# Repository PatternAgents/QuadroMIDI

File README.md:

# QuadroMIDI - Four channel MIDI Trigger I/O

Format : ERA / Eurorack / Breadboard Friendly

Height : 1U 

Width: 16HP

Depth : 1.0 cm

Power : +12V 40mA, -12V 40mA

Jacks : Thonkiconn Jacks (PJ301M-12)

The QuadroMIDI is a low cost, embeddable MIDI Trigger module

* Embedded Rack Architecture (Eurorack compatible)
* Optically Isolated MIDI Input Jack
* Driven MIDI Output Jack
* MIDI Clock Output Jack
* MIDI Run/Stop Output Jack
* Four (4) DC coupled  Trigger input channels
* Four (4) DC coupled  Trigger output channels
* Add an optional Front-Panel board for mounting in ERA and/or Eurorack enclosures

[QuadroMIDI](https://github.com/patternagents/QuadroMIDI)

**thingSoC ERA** are OEM friendly implementations that implement various reference 
circuits for demonstrating the use of the PatternAgents IP and Libraries.

---------------------------------------
## QuadroMIDI Applications <a name="QuadroMIDI_Applications"/>

* MIDI to Trigger (Drum Piezo or other Human Interface)
* Add-on board for QuadroTeenia (MIDI I/O and Trigger I/O)

---------------------------------------
## QuadroMIDI Status <a name="QuadroMIDI_Status"/>

**4/10/2018:** 
Revision 1.0.0 - Initial Layout sent from OSHpark

---------------------------------------
## QuadroMIDI Model Images

[QuadroMIDI](https://github.com/patternagents/QuadroMIDI)

[QuadroMIDI](https://github.com/patternagents/QuadroMIDI)

---------------------------------------

## QuadroMIDI Documentation Index <a name="QuadroMIDI_documentation_index"/>

[QuadroMIDI Project](http://thingsoc.github.io/projects/QuadroMIDI.html)

[QuadroMIDI Hardware](https://github.com/patternagents/QuadroMIDI/tree/master/QuadroMIDI/revisions/R1_0_0)

---------------------------------------

## Documentation Index <a name="documentation_index"/>

[Organization Website](http://patternagents.github.io)

[FAQ - Frequently Asked Questions](http://thingsoc.github.io/support/faq.html)

---------------------------------------

[ 
*PatternAgents, LLC*](http://thingsoc.github.io)

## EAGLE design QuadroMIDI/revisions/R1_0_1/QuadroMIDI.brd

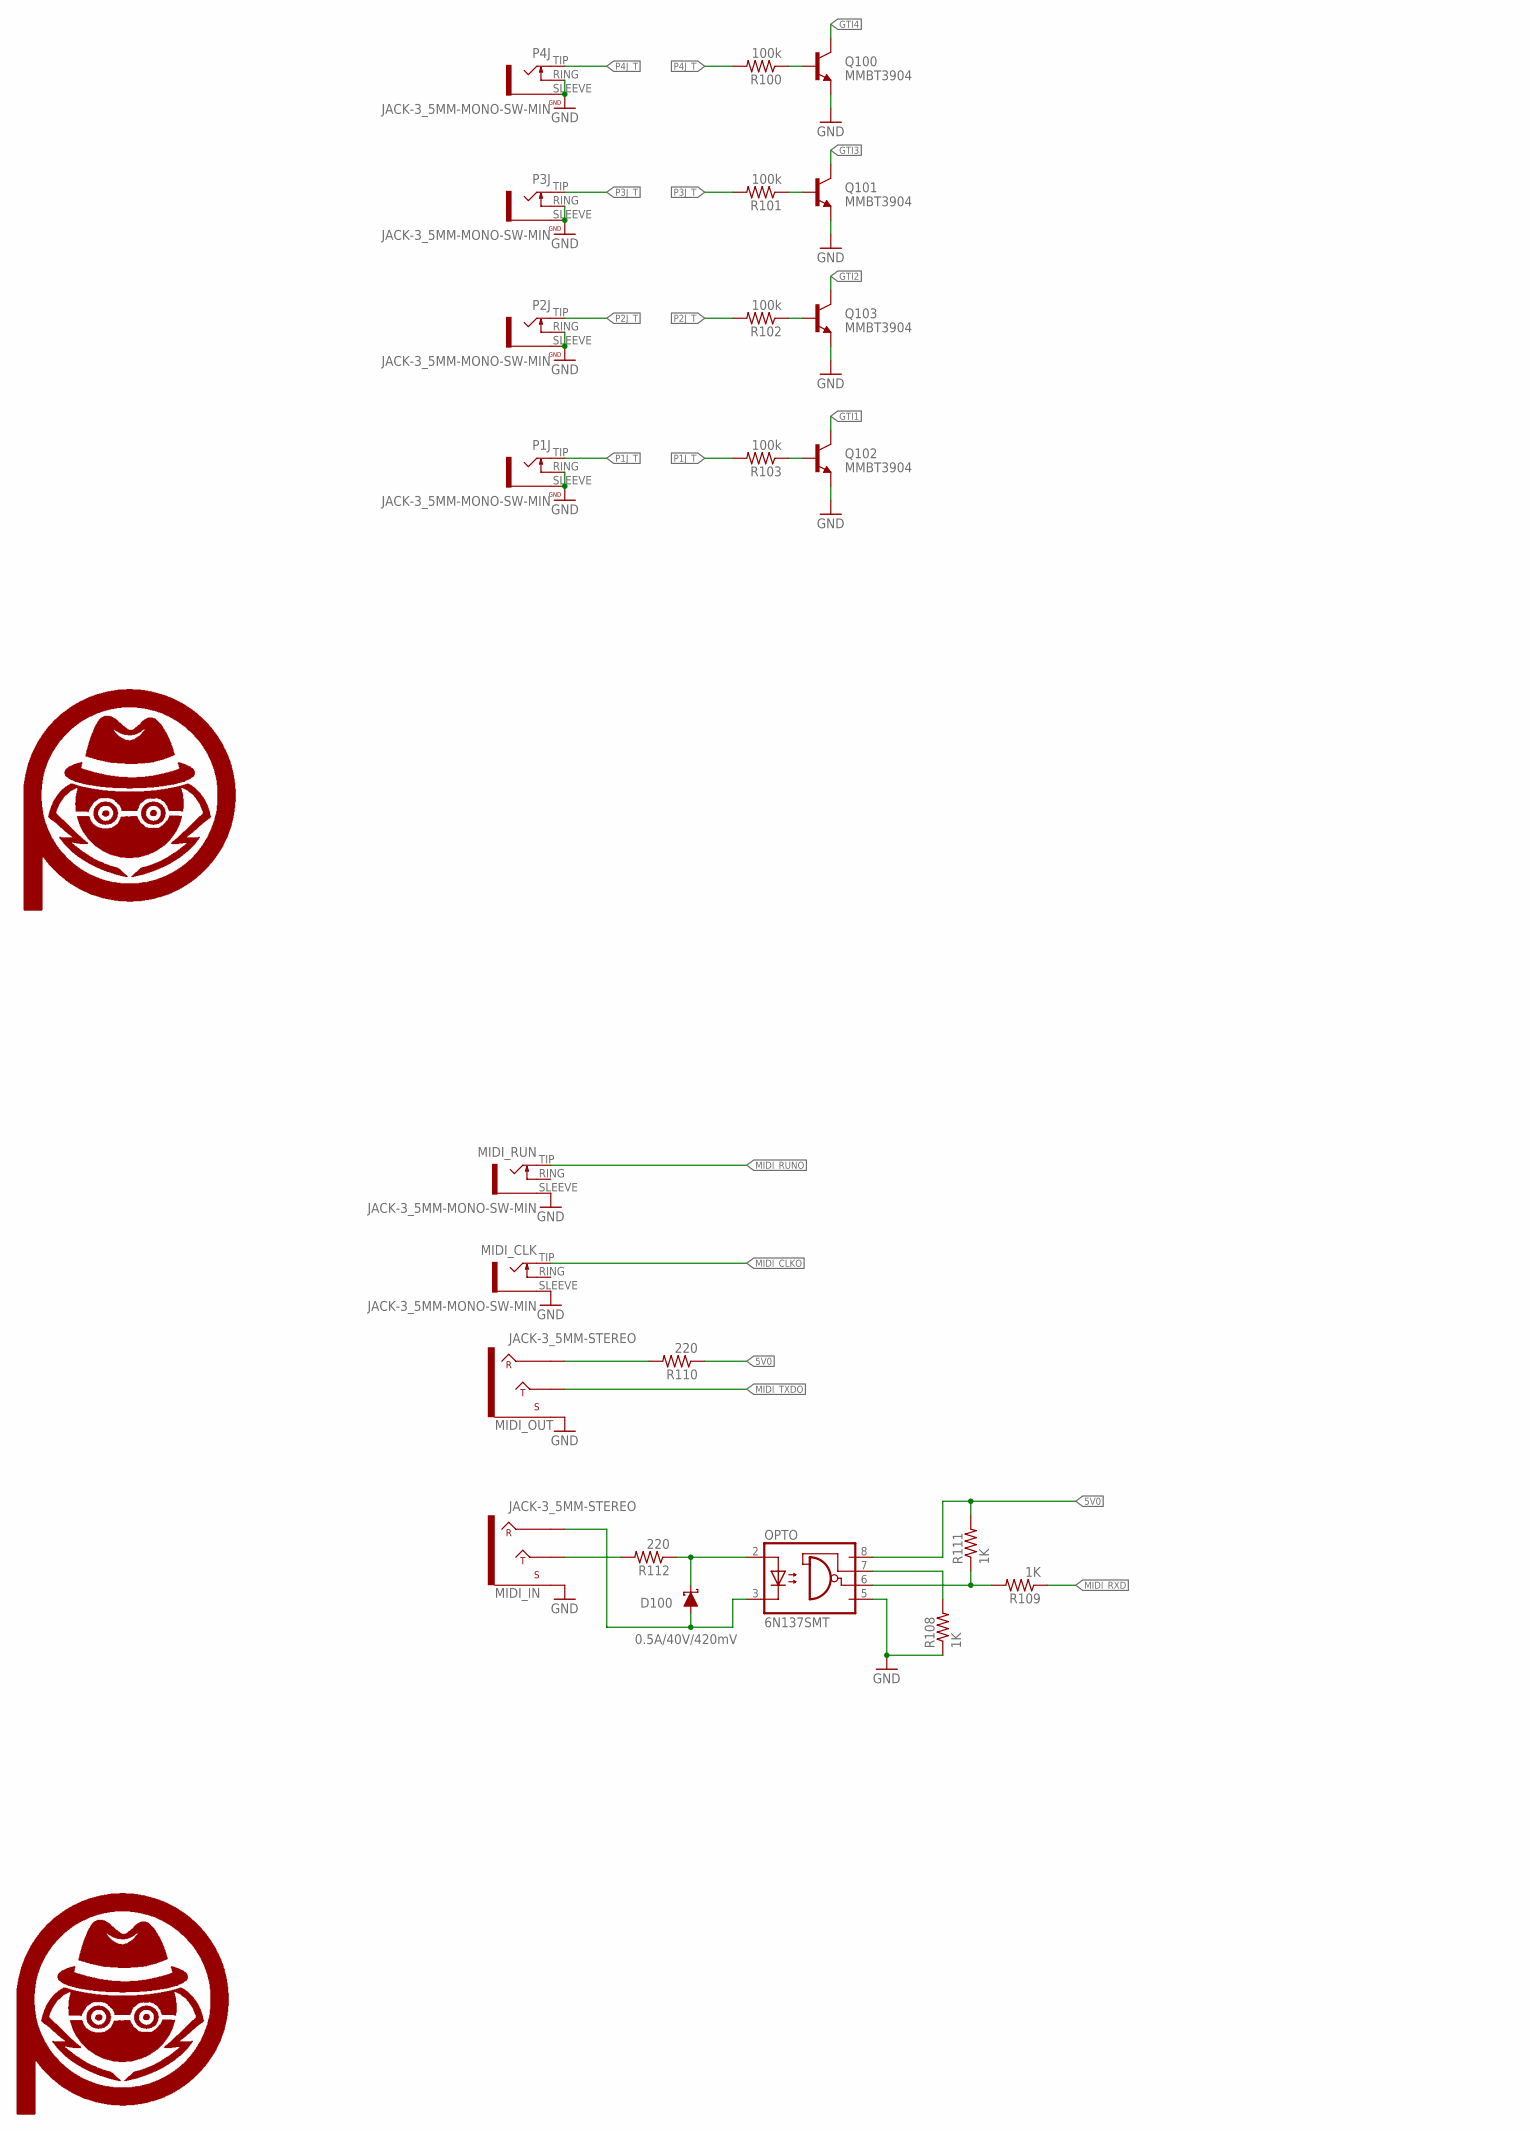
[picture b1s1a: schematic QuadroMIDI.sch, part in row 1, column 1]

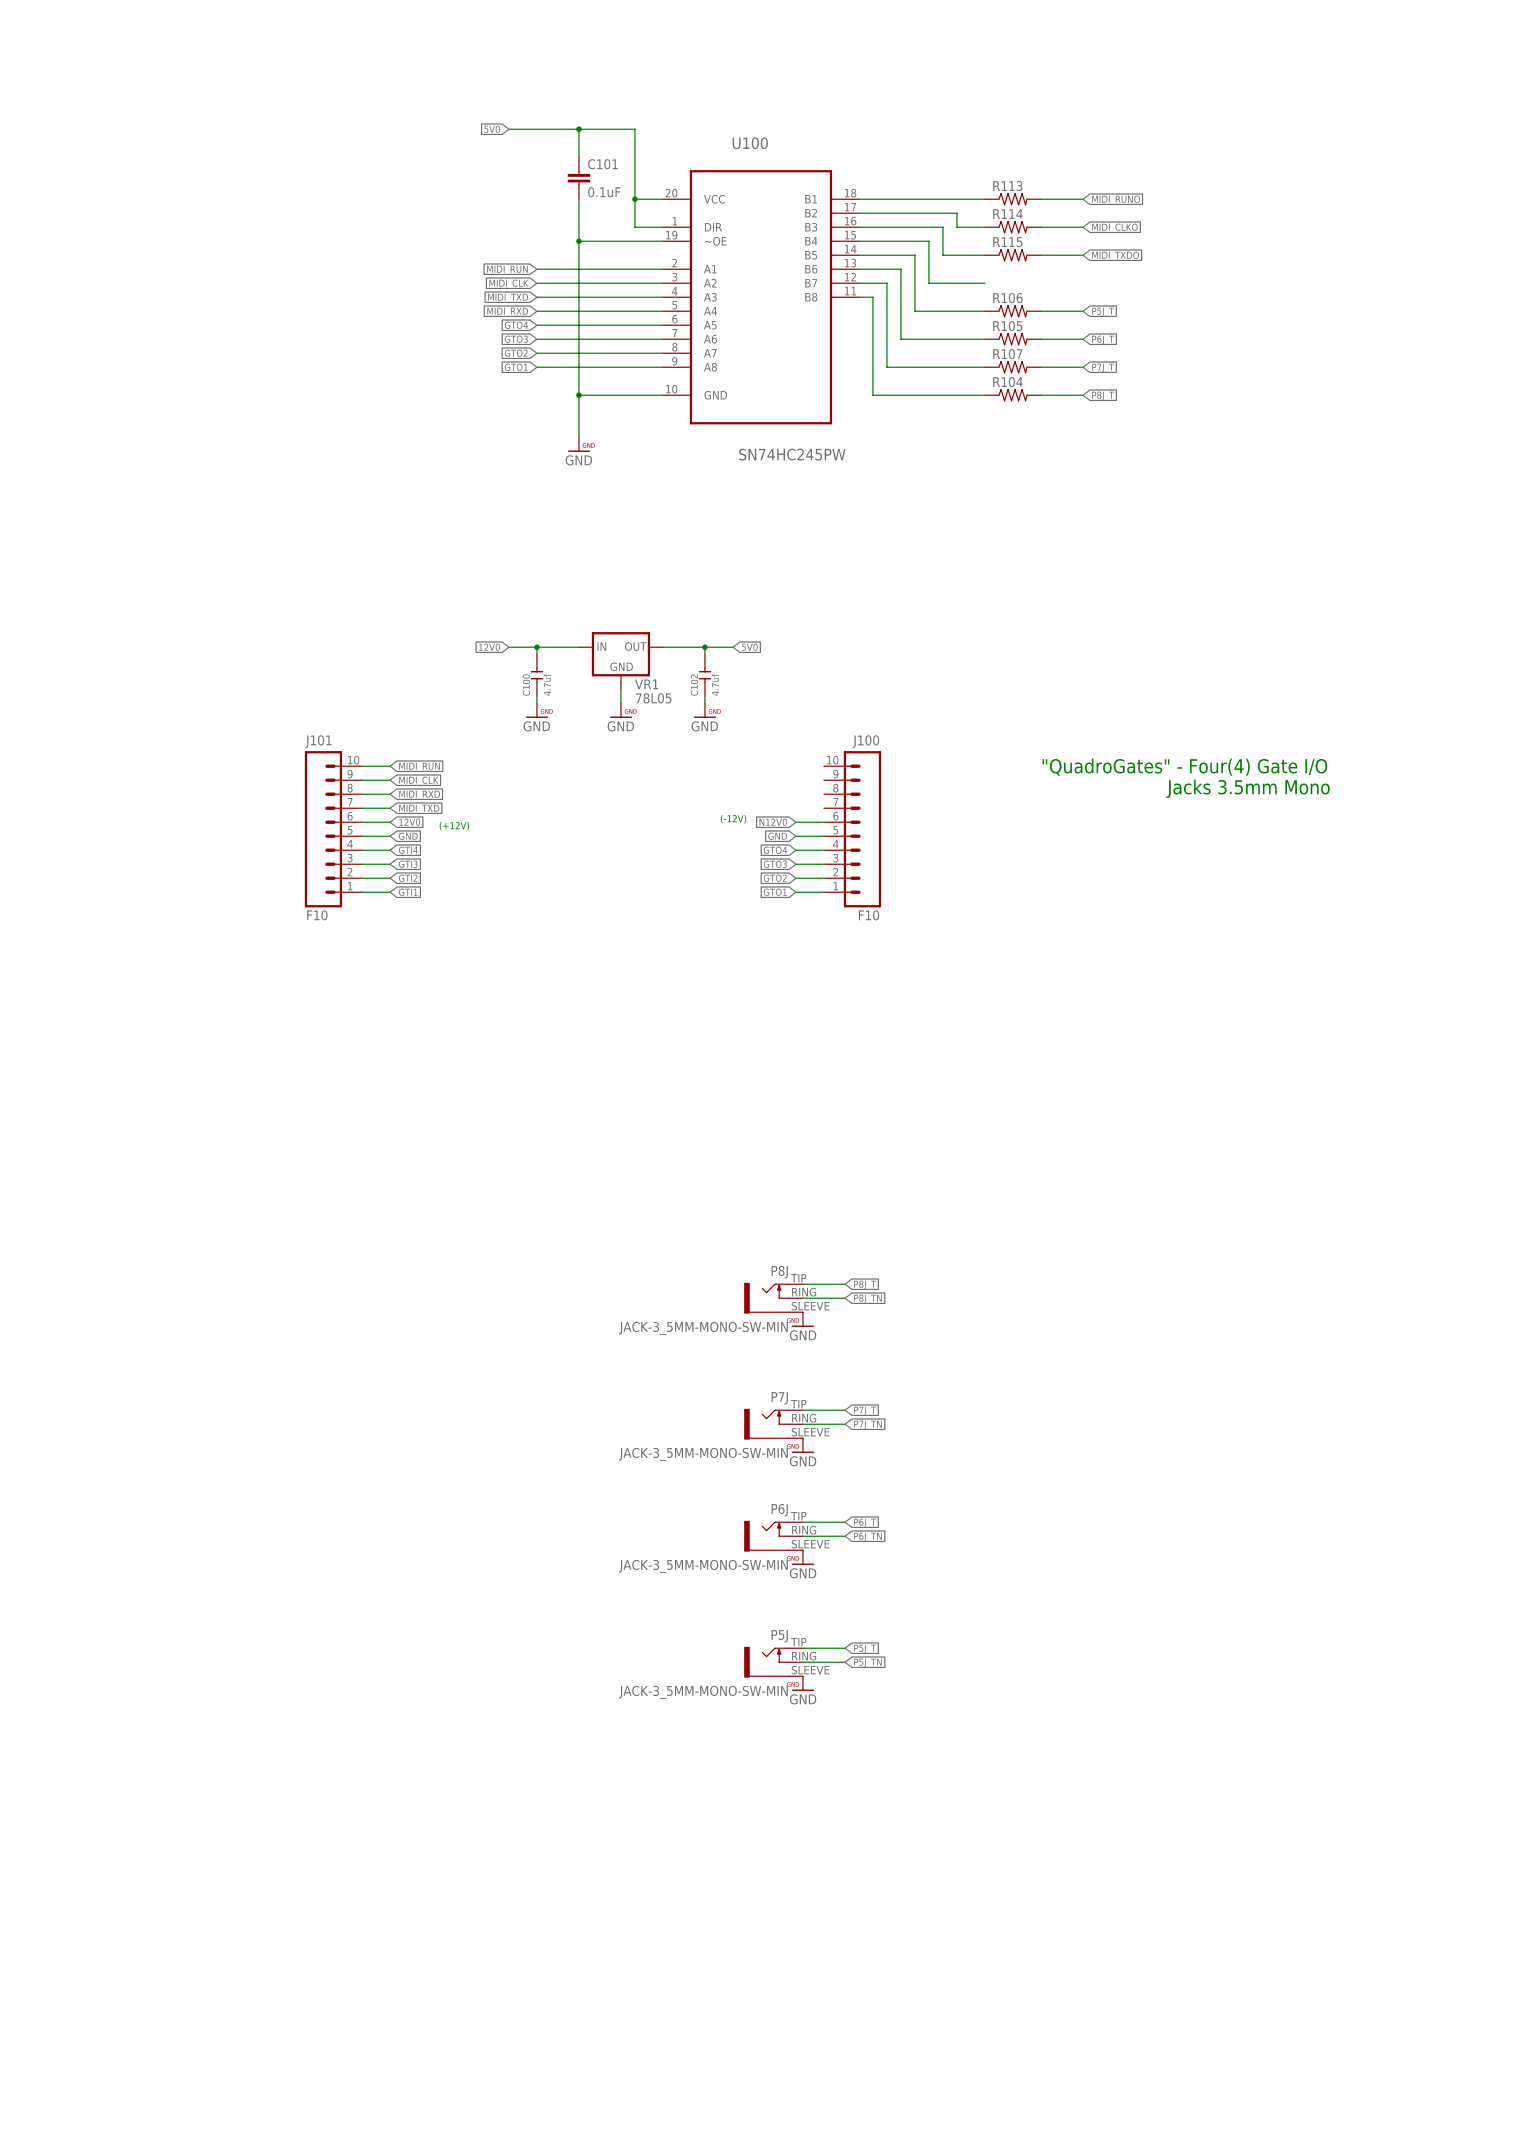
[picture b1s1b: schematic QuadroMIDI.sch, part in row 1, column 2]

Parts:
$$U$1: PA_LOGO_SYMLARGE; PA_LOGO_AGENT_LRG_SYM
C100, C102: 4.7uf; C0805
C101: 0.1uF; 0603-CAP
D100: 0.5A/40V/420mV; SOD-323
J100, J101: F10; 1X10_OCTO
MIDI_CLK: JACK-3_5MM-MONO-SW-MIN; WQP_PJ301M-MIN
MIDI_IN: JACK-3_5MM-STEREO; WQP_PJ301M-MIN
MIDI_OUT: JACK-3_5MM-STEREO; WQP_PJ301M-MIN
MIDI_RUN: JACK-3_5MM-MONO-SW-MIN; WQP_PJ301M-MIN
OPTO: 6N137SMT; DIL8-SMD
P1J, P2J, P3J, P4J, P5J, P6J, P7J, P8J: JACK-3_5MM-MONO-SW-MIN; WQP_PJ301M-MIN
Q100, Q101, Q102, Q103: MMBT3904; SOT23-BEC
R100, R101, R102, R103: 100k; R0603
R104, R105, R106, R107, R113, R114, R115: RESISTOR0603-RES; 0603-RES
R108, R109, R111: 1K; 0603-RES
R110, R112: 220; 0603-RES
U100: SN74HC245PW; SOP65P640X120-20N
U$100: PA_LOGO_SYMSMALL; PA_LOGO_AGENT_SMALL_SYM
VR1: 78L05; SOT89

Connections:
5V0: C101.1, C102.2, OPTO.8 (VCC), R110.1, R111.2, U100.1 (DIR), U100.20 (VCC), VR1.1 (OUT)
12V0: C100.2, J101.6, VR1.3 (IN)
B1: R113.1, U100.18 (B1)
B2: R114.1, U100.17 (B2)
B3: R115.1, U100.16 (B3)
B4: U100.15 (B4)
B5: R106.1, U100.14 (B5)
B6: R105.1, U100.13 (B6)
B7: R107.1, U100.12 (B7)
B8: R104.1, U100.11 (B8)
GND: C100.1, C101.2, C102.1, J100.5, J101.5, MIDI_CLK.SLEEVE, MIDI_IN.SLEEVE, MIDI_OUT.SLEEVE, MIDI_RUN.SLEEVE, OPTO.5 (GND), P1J.RING (TIP_SW), P1J.SLEEVE, P2J.RING (TIP_SW), P2J.SLEEVE, P3J.RING (TIP_SW), P3J.SLEEVE, P4J.RING (TIP_SW), P4J.SLEEVE, P5J.SLEEVE, P6J.SLEEVE, P7J.SLEEVE, P8J.SLEEVE, Q100.E, Q101.E, Q102.E, Q103.E, R108.1, U100.10 (GND), U100.19 (~OE), VR1.2 (GND)
GTI1: J101.1, Q102.C
GTI2: J101.2, Q103.C
GTI3: J101.3, Q101.C
GTI4: J101.4, Q100.C
GTO1: J100.1, U100.9 (A8)
GTO2: J100.2, U100.8 (A7)
GTO3: J100.3, U100.7 (A6)
GTO4: J100.4, U100.6 (A5)
MIDIP: MIDI_IN.TIP, R112.2
MIDIRX: OPTO.6 (VO), R109.2, R111.1
MIDI_CLK: J101.9, U100.3 (A2)
MIDI_CLKO: MIDI_CLK.TIP, R114.2
MIDI_RUN: J101.10, U100.2 (A1)
MIDI_RUNO: MIDI_RUN.TIP, R113.2
MIDI_RXD: J101.8, R109.1, U100.5 (A4)
MIDI_TXD: J101.7, U100.4 (A3)
MIDI_TXDO: MIDI_OUT.TIP, R115.2
MIDN: D100.A, MIDI_IN.RING, OPTO.3 (C)
MIDP: D100.C, OPTO.2 (A), R112.1
N12V0: J100.6
unnamed: Q102.B, R103.1
unnamed: Q103.B, R102.1
unnamed: MIDI_OUT.RING, R110.2
unnamed: Q101.B, R101.1
unnamed: Q100.B, R100.1
OPTO: OPTO.7 (VE), R108.2
P1J_T: P1J.TIP, R103.2
P2J_T: P2J.TIP, R102.2
P3J_T: P3J.TIP, R101.2
P4J_T: P4J.TIP, R100.2
P5J_T: P5J.TIP, R106.2
P5J_TN: P5J.RING (TIP_SW)
P6J_T: P6J.TIP, R105.2
P6J_TN: P6J.RING (TIP_SW)
P7J_T: P7J.TIP, R107.2
P7J_TN: P7J.RING (TIP_SW)
P8J_T: P8J.TIP, R104.2
P8J_TN: P8J.RING (TIP_SW)

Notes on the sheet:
(+12V)
(-12V)
"QuadroGates" - Four(4) Gate I/O Jacks 3.5mm Mono

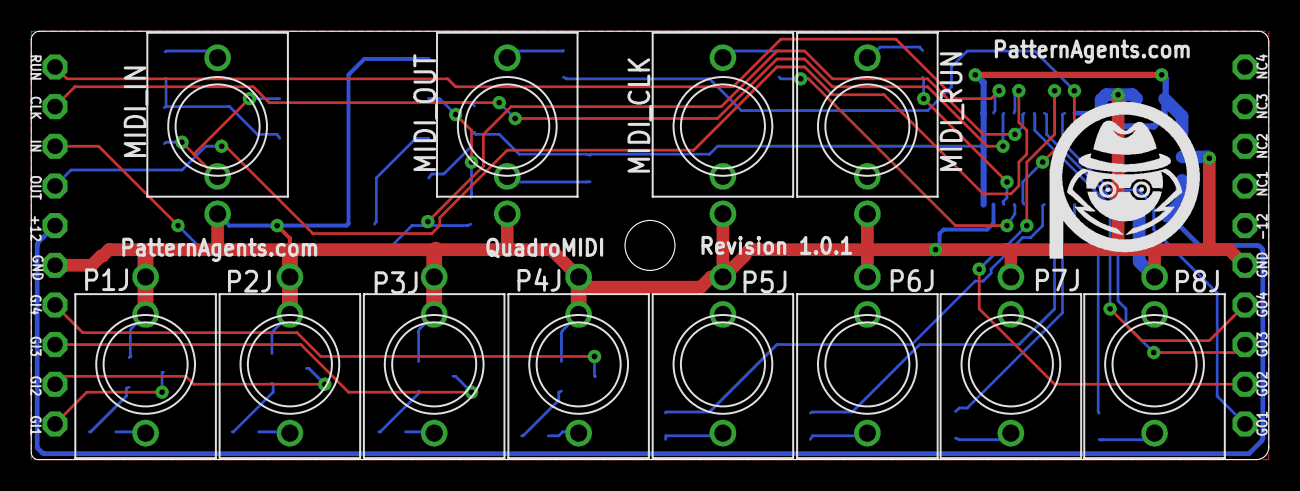
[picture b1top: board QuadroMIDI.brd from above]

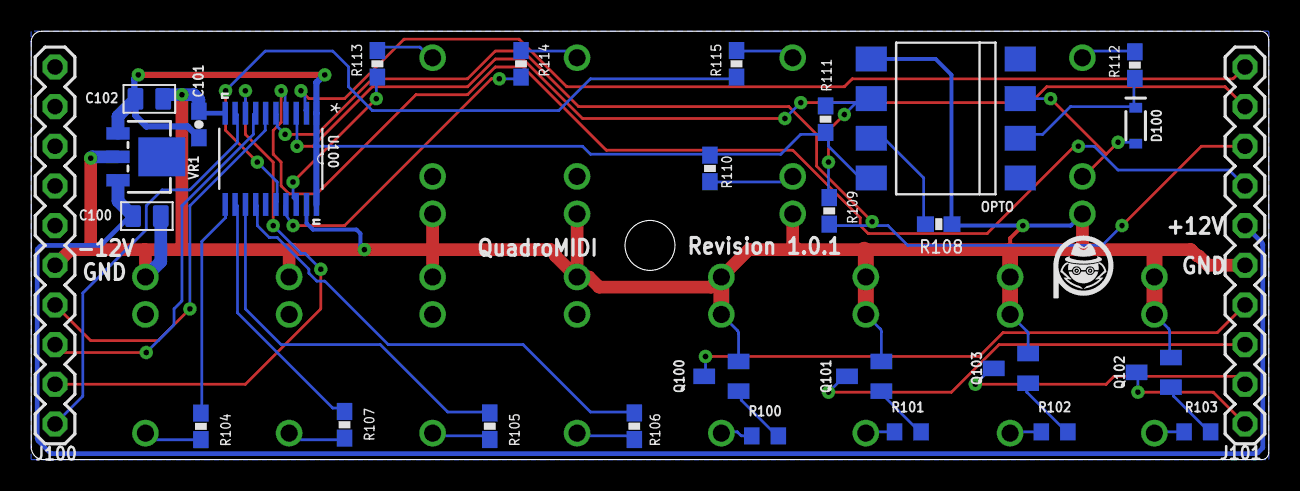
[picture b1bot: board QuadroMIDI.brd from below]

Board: 2 copper layers, 79.2 x 27.4 mm, 43 parts (30 on the bottom side), 43 nets.

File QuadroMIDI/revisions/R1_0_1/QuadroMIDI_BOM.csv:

"Qty";"Value";"Device";"Package";"Parts";"Description";"";
"7";"";"RESISTOR0603-RES";"0603-RES";"R104, R105, R106, R107, R113, R114, R115";"Resistor";"";
"1";"0.1uF";"CAP0603-CAP";"0603-CAP";"C101";"Capacitor";"";
"1";"0.5A/40V/420mV";"DIODE-SCHOTTKY-PMEG4005EJ";"SOD-323";"D100";"Schottky diode";"";
"4";"100k";"R-US_R0603";"R0603";"R100, R101, R102, R103";"RESISTOR, American symbol";"";
"3";"1K";"RESISTOR0603";"0603-RES";"R108, R109, R111";"Resistor";"";
"2";"220";"RESISTOR0603";"0603-RES";"R110, R112";"Resistor";"";
"2";"4.7uf";"CERAMIC-4.7UF-25V-10%-X5R(0805)";"C0805";"C100, C102";"302010146";"";
"1";"6N137SMT";"6N137SMT";"DIL8-SMD";"OPTO";"MOTOROLA OPTO COUPLER";"";
"1";"78L05";"78LXX-SOT89";"SOT89";"VR1";"VOLTAGE REGULATOR";"";
"2";"F10";"M10SILK_FEMALE_PTH";"1X10_OCTO";"J100, J101";"Header 10";"";
"10";"JACK-3_5MM-MONO-SW-MIN";"JACK-3_5MM-MONO-SW-MIN";"WQP_PJ301M-MIN";"MIDI_CLK, MIDI_RUN, P1J, P2J, P3J, P4J, P5J, P6J, P7J, P8J";"Jack, 3.5mm, RIght Angle, Though-Hole";"";
"2";"JACK-3_5MM-STEREO";"JACK-3_5MM-STEREO";"WQP_PJ301M-MIN";"MIDI_IN, MIDI_OUT";"Stereo 3.5mm Jack (TRS - Tip, Ring, Sleeve)";"";
"4";"MMBT3904";"MMBT3904LT1-NPN-SOT23-BEC";"SOT23-BEC";"Q100, Q101, Q102, Q103";"NPN Transistror";"";
"1";"PA_LOGO_SYMLARGE";"PA_LOGO_SYMLARGE";"PA_LOGO_AGENT_LRG_SYM";"$$U$1";"PatternAgents Logo Symbol";"";
"1";"PA_LOGO_SYMSMALL";"PA_LOGO_SYMSMALL";"PA_LOGO_AGENT_SMALL_SYM";"U$100";"PatternAgents Logo Symbol";"";
"1";"SN74HC245PW";"SN74HC245PW";"SOP65P640X120-20N";"U100";"OCTAL BUS TRANSCEIVERS";"";

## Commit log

2018-04-09 initial version
2018-04-10 4/10 update
2018-04-11 4/11 update
2018-04-12 First Release

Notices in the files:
README.md:
License: CC BY-NC 4.0
parts and their libraries:
PatternAgents-Logos: License : http://creativecommons.org/licenses/by-sa/3.0
(Creative Commons 3.0)
PatternAgents-ProtoPads: License : http://creativecommons.org/licenses/by-sa/4.0
(Creative Commons 4.0)
